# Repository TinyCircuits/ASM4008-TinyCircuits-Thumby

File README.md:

# ASM4008 TinyCircuits Thumby

The design files are located under design_files/ for the TinyCircuits ASM4008 PCB. *Note: Rev 6 is the latest and current version of Thumby being built and shipped. Early Kickstarter units shipped with Rev 5 Thumby hardware - Rev 6 updates were made during fulfillment to decrease manufacturing and assembly time.* This is a RP2040 board that is programmable using Arduino, Thonny, or any preferred MicroPython IDE. We recommend using our web browser [Thumby Code Editor](https://code.thumby.us/) for MicroPython.

Format is in Cadsoft Eagle format - Eagle version 6.2 was used for the original design.

For more infomation, check out the [Thumby product page](https://tinycircuits.com/thumby) at TinyCircuits.com

Other helpful Thumby Links:

- [Thumby Documentation Site](https://thumby.us/)  
   -  Contribute to Thumby Documentation at the [Thumby Doc Site Repository](https://github.com/TinyCircuits/Thumby-Website)
- [Thumby Code Editor](https://code.thumby.us/)
   - Contrbute to the [Thumby Code Editor Repository](https://github.com/TinyCircuits/TinyCircuits-Thumby-Code-Editor)
- [Thumby Arcade](https://arcade.thumby.us/)
   - Contribute a game to the [Thumby Game Repository](https://github.com/TinyCircuits/TinyCircuits-Thumby-Games)

# License:

Design by TinyCircuits.
All design files are released under the Creative Commons Attribution Share-Alike 3.0 License, see the following link for details: http://creativecommons.org/licenses/by-sa/3.0

All text above must be included in any redistribution or derived design

This project uses designs and concepts developed as part of the Arduino project and the LilyPad project.  The TinyCircuits design files themselves (schematics, PCB and libraries) are not directly derived from these works' design files and have been created new, however the concepts and basic architecture behind the TinyDuino and TinyLily products are derived and we thank the hard work of the organizations below for their contributions to open-source hardware:
  
Original Arduino Uno Design by Team Arduino

LilyPad Arduino Design by Leah Buechley and Sparkfun Electronics

Please support the open-source hardware community

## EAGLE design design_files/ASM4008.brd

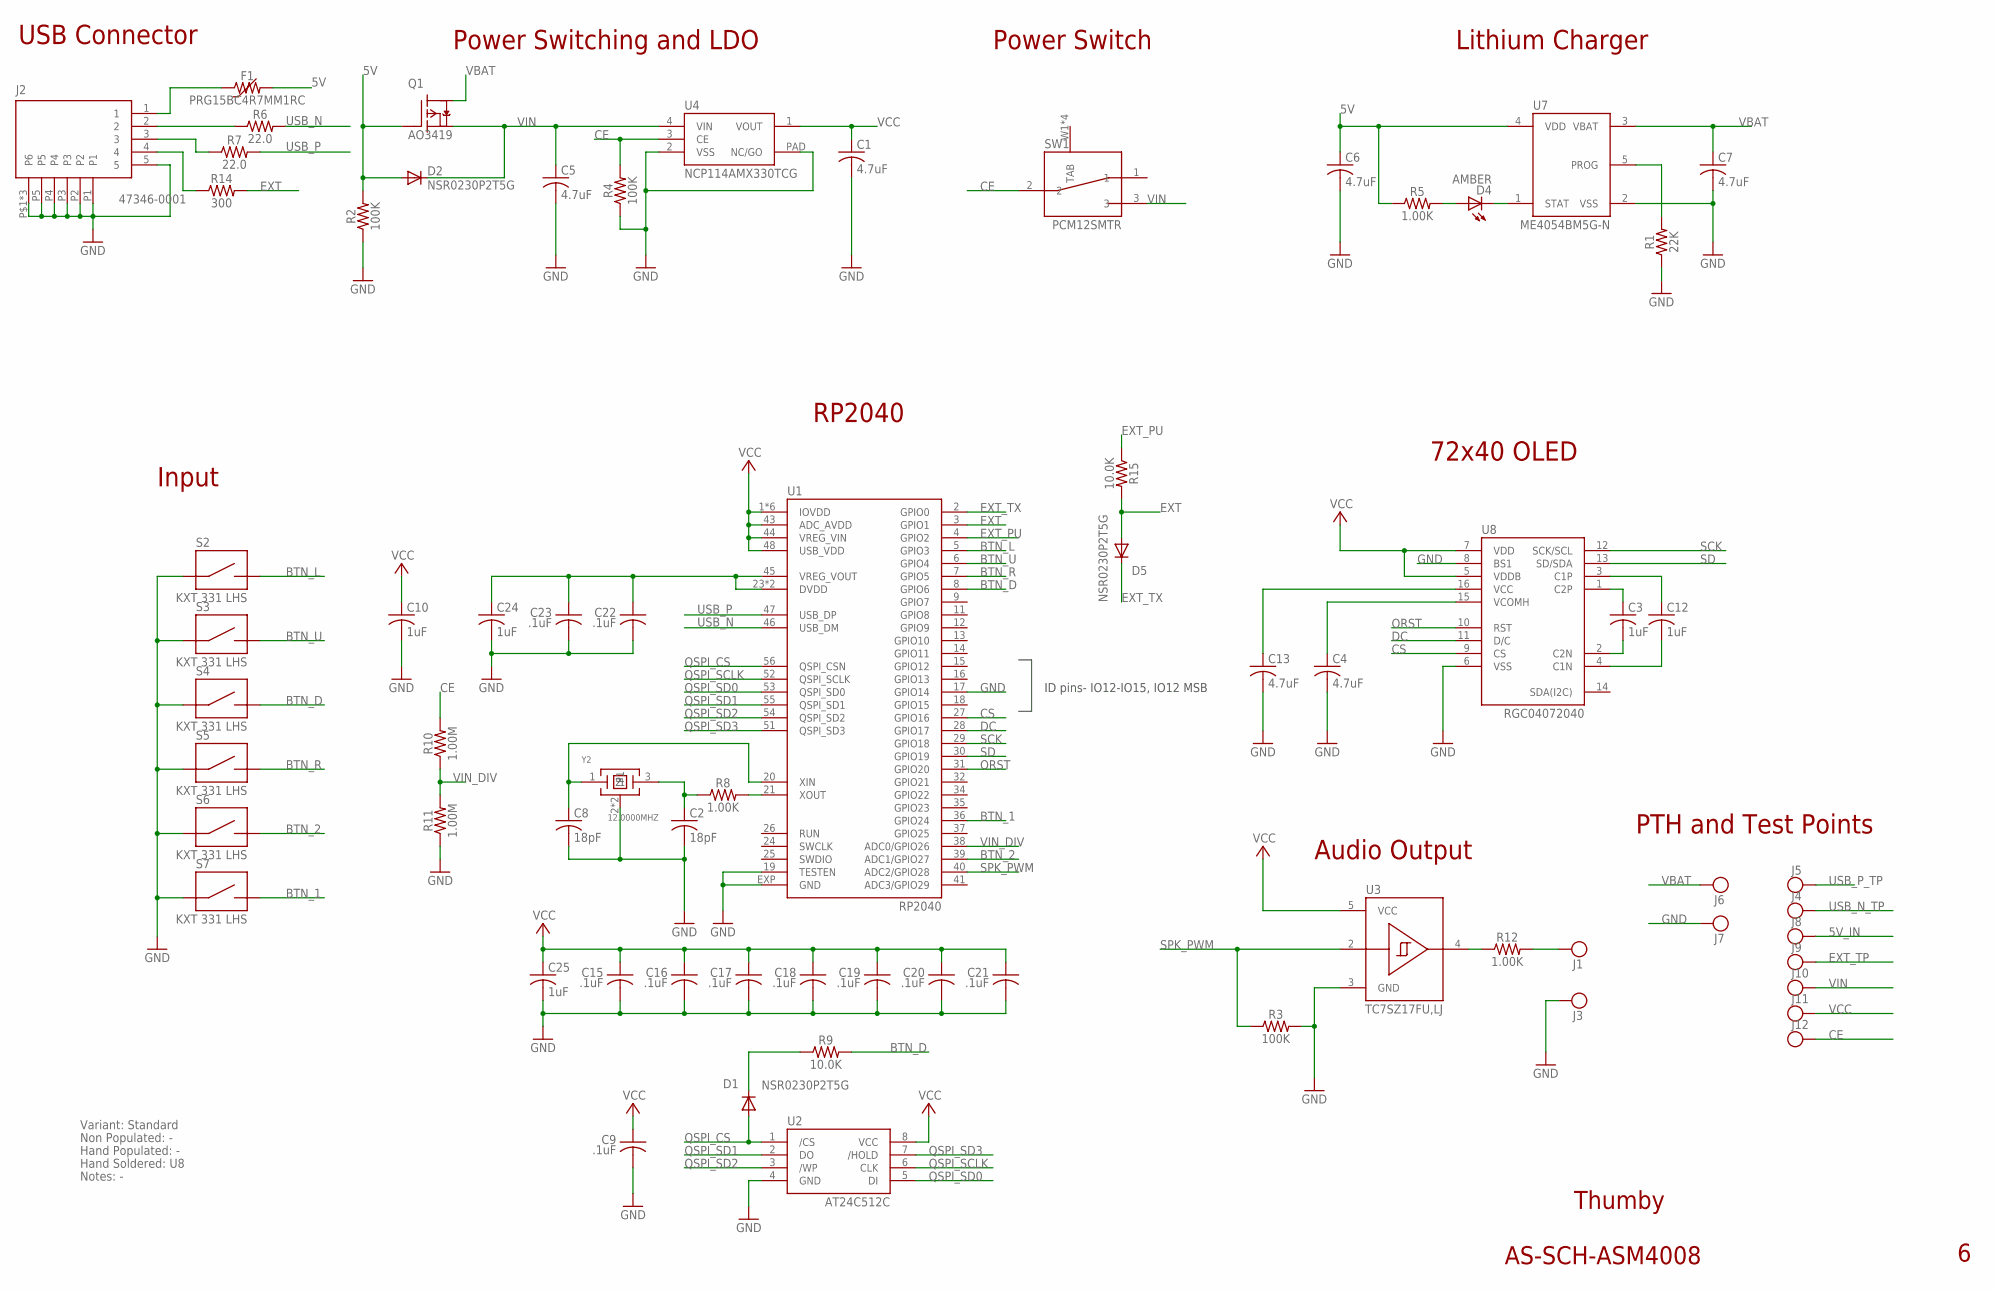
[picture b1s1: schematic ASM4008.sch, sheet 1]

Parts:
C1, C5: 4.7uF; C0402; PARTNO AS-ITM-00242
C2, C8: 18pF; C0402
C3, C10, C12: 1uF; C0603
C4, C13: 4.7uF; C0603
C6, C7: 4.7uF; C0402
C9, C22, C23: .1uF; C0402
C15, C16, C17, C18, C19, C20, C21: .1uF; C0402; PARTNO AS-ITM-00008
C24, C25: 1uF; C0402
D1, D2, D5: NSR0230P2T5G; SOD-923L
D4: AMBER; 0402_LED
F1: PRG15BC4R7MM1RC; 0402
J1, J3: 2336713-2
J2: 47346-0001; MICRO_USB_TABS
J4, J5, J8, J9, J10, J11, J12: TEST_POINT; TEST_POINT_1MM
J6, J7: PIN_1X.1"; 1X.1"
Q1: AO3419; SOT23A
R1: 22K; 0402
R2, R3, R4: 100K; 0402
R5, R8, R12: 1.00K; 0402
R6, R7: 22.0; 0402
R9, R15: 10.0K; 0402
R10, R11: 1.00M; 0402
R14: 300; 0402
S2, S3, S4, S5, S6, S7: KXT 331 LHS; KXT_LHS_1
SW1: PCM12SMTR; PCM12SMTR_THUMBY
U1: RP2040; QFN56_0.4
U2: AT24C512C; UDFN-8-NP; PARTNO AS-ITM-00628
U3: TC7SZ17FU,LJ; SOT-353-NOPAD; PARTNO AS-ITM-00647
U4: NCP114AMX330TCG; 4-UFDN
U7: ME4054BM5G-N; SOT-23
U8: RGC04072040; OLED_042
Y2: 12.0000MHZ; CRYSTAL_2.5X2MM_4SMD

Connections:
5V: C6.1, D2.A, F1.2, Q1.B (G), R2.2, R5.1, U7.4 (VDD)
5V_IN: F1.1, J2.1, J8.P$1
BTN_1: S7.2, U1.36 (GPIO24)
BTN_2: S6.2, U1.39 (ADC1/GPIO27)
BTN_D: R9.2, S4.2, U1.8 (GPIO6)
BTN_L: S2.2, U1.5 (GPIO3)
BTN_R: S5.2, U1.7 (GPIO5)
BTN_U: S3.2, U1.6 (GPIO4)
CE: J12.P$1, R4.2, R10.2, SW1.2, U4.3 (CE)
CS: U1.27 (GPIO16), U8.9 (CS)
DC: U1.28 (GPIO17), U8.11 (D/C)
EXT: D5.A, R14.2, R15.2, U1.3 (GPIO1)
EXT_PU: R15.1, U1.4 (GPIO2)
EXT_TP: J2.4, J9.P$1, R14.1
EXT_TX: D5.C, U1.2 (GPIO0)
GND: C1.2, C2.2, C4.2, C5.2, C6.2, C7.2, C8.2, C9.2, C10.2, C13.2, C15.2, C16.2, C17.2, C18.2, C19.2, C20.2, C21.2, C22.2, C23.2, C24.2, C25.2, J2.5, J2.P1, J2.P2, J2.P3, J2.P4, J2.P5, J2.P6, J2.P$1 (P6), J2.P$2 (P6), J3.P$1, J7.1, R1.1, R2.1, R3.2, R4.1, R11.1, S2.1, S3.1, S4.1, S5.1, S6.1, S7.1, U1.17 (GPIO14), U1.19 (TESTEN), U1.EXP (GND), U2.4 (GND), U3.3 (GND), U4.2 (VSS), U4.PAD (NC/GO), U7.2 (VSS), U8.6 (VSS), U8.8 (BS1), Y2.2 (P1), Y2.4 (P1)
unnamed: D4.2 (C), U7.1 (STAT)
unnamed: D4.1 (A), R5.2
unnamed: R1.2, U7.5 (PROG)
unnamed: D1.C, R9.1
unnamed: J1.P$1, R12.2
unnamed: C22.1, C23.1, C24.1, U1.23 (DVDD), U1.45 (VREG_VOUT), U1.50 (DVDD)
unnamed: R8.2, U1.21 (XOUT)
unnamed: C8.1, U1.20 (XIN), Y2.1
unnamed: C2.1, R8.1, Y2.3 (2)
unnamed: R12.1, U3.4 (Y)
unnamed: C4.1, U8.15 (VCOMH)
unnamed: C13.1, U8.16 (VCC)
unnamed: C3.1, U8.1 (C2P)
unnamed: C12.1, U8.3 (C1P)
unnamed: C3.2, U8.2 (C2N)
unnamed: C12.2, U8.4 (C1N)
ORST: U1.31 (GPIO20), U8.10 (RST)
QSPI_CS: D1.A, U1.56 (QSPI_CSN), U2.1 (/CS)
QSPI_SCLK: U1.52 (QSPI_SCLK), U2.6 (CLK)
QSPI_SD0: U1.53 (QSPI_SD0), U2.5 (DI)
QSPI_SD1: U1.55 (QSPI_SD1), U2.2 (DO)
QSPI_SD2: U1.54 (QSPI_SD2), U2.3 (/WP)
QSPI_SD3: U1.51 (QSPI_SD3), U2.7 (/HOLD)
SCK: U1.29 (GPIO18), U8.12 (SCK/SCL)
SD: U1.30 (GPIO19), U8.13 (SD/SDA)
SPK_PWM: R3.1, U1.40 (ADC2/GPIO28), U3.2 (A)
USB_N: R6.2, U1.46 (USB_DM)
USB_N_TP: J2.2, J4.P$1, R6.1
USB_P: R7.2, U1.47 (USB_DP)
USB_P_TP: J2.3, J5.P$1, R7.1
VBAT: C7.1, J6.1, Q1.C (D), U7.3 (VBAT)
VCC: C1.1, C9.1, C10.1, C15.1, C16.1, C17.1, C18.1, C19.1, C20.1, C21.1, C25.1, J11.P$1, U1.1 (IOVDD), U1.10 (IOVDD), U1.22 (IOVDD), U1.33 (IOVDD), U1.42 (IOVDD), U1.43 (ADC_AVDD), U1.44 (VREG_VIN), U1.48 (USB_VDD), U1.49 (IOVDD), U2.8 (VCC), U3.5 (VCC), U4.1 (VOUT), U8.5 (VDDB), U8.7 (VDD)
VIN: C5.1, D2.C, J10.P$1, Q1.E (S), SW1.3, U4.4 (VIN)
VIN_DIV: R10.1, R11.2, U1.38 (ADC0/GPIO26)

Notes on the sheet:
Thumby
AS-SCH-ASM4008
Lithium Charger
Power Switching and LDO
72x40 OLED
RP2040
Variant: Standard
Non Populated: -
Hand Populated: -
Hand Soldered: U8
Notes: -
USB Connector
Power Switch
Input
Audio Output
ID pins- IO12-IO15, IO12 MSB
PTH and Test Points

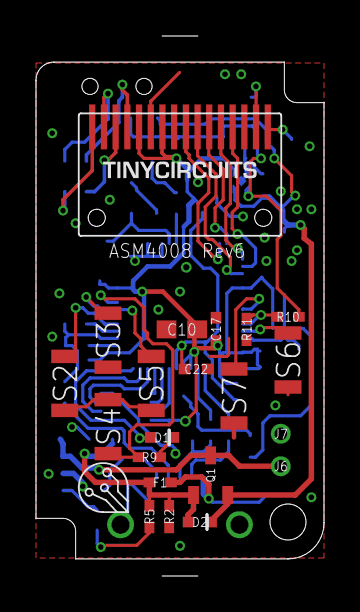
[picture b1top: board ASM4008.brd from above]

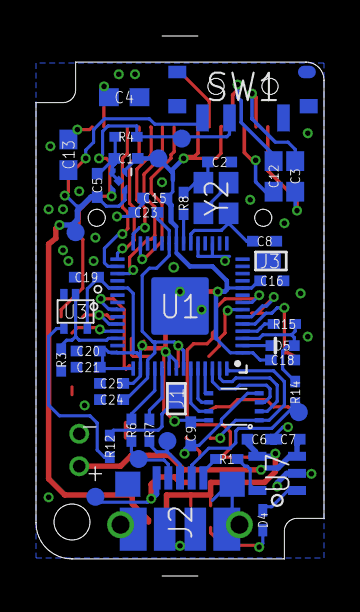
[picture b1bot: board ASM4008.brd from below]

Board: 2 copper layers, 16.0 x 30.0 mm, 70 parts (48 on the bottom side), 50 nets.

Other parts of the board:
U$1: DOCFIELD-TINYCIRCUITS-PCB

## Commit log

2022-06-21 design files
2022-06-21 Add Thumby STL
2022-06-21 Link Cable connection
2023-02-08 make stl easier to download
2023-02-09 Update Thumby stl zip to include separated files
